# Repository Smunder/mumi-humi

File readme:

Information and project documentationa at https://smundor.de/category/mumi-humi/

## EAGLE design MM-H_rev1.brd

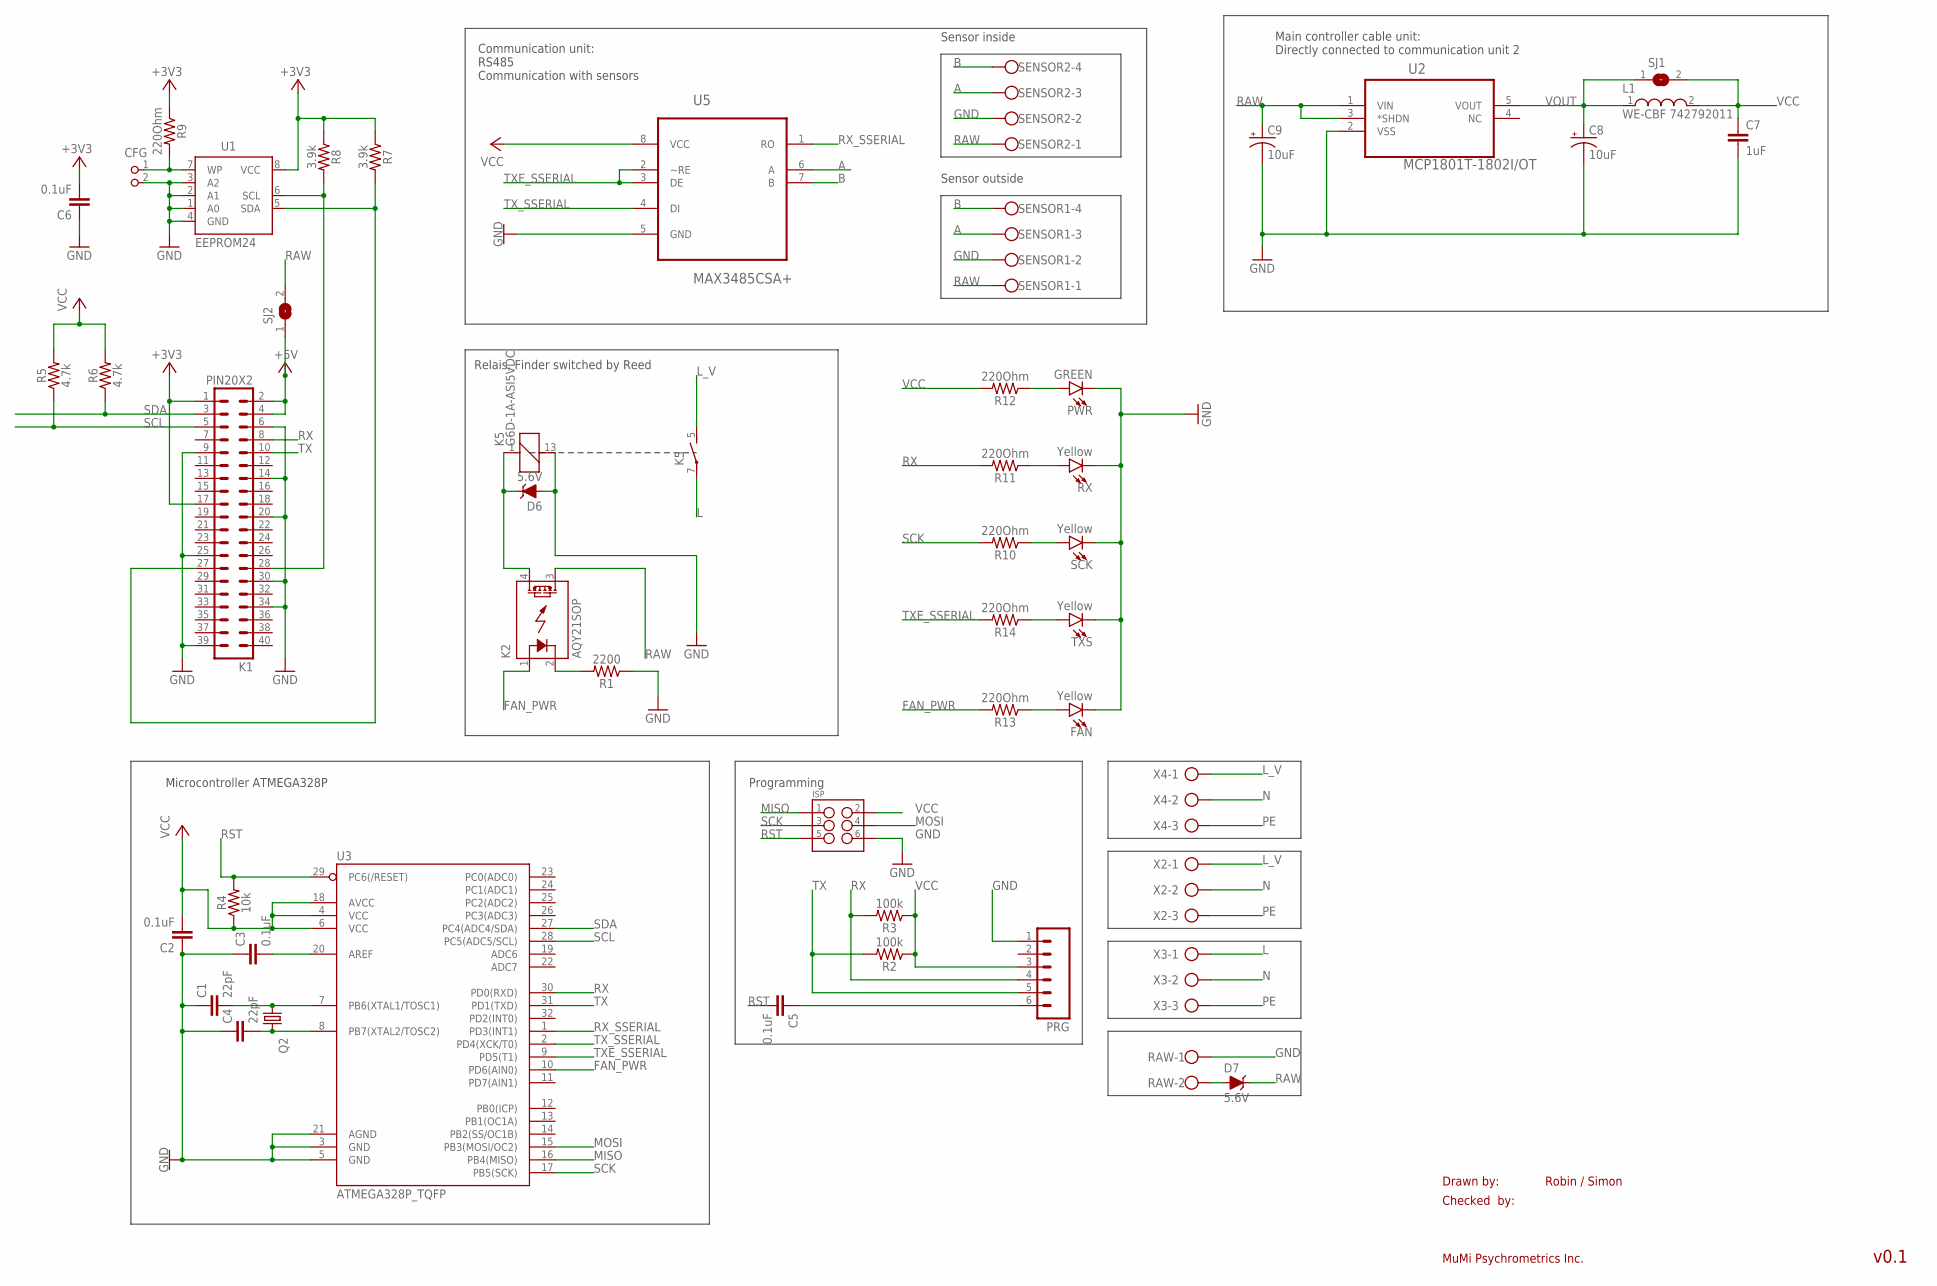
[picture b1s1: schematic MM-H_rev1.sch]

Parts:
C1, C4: 22pF; 0402
C2, C3, C5, C6: 0.1uF; 0402
C7: 1uF; 0402
C8, C9: 10uF; EIA3216
CFG: PIN2_100; PIN_W_2
D6, D7: 5.6V; SOD-323
FAN: Yellow; LED-0603
ISP: M03X2POGO_PINS; 2X3_POGO
K1: PIN20X2; PIN_20X2
K2: AQY21SOP; SOP04
K5: G6D-1A-ASI5VDC; G6D
L1: WE-CBF 742792011; WE-CBF_0805(W=3.0)
PRG: M06SILK_FEMALE_PTH; 1X06
PWR: GREEN; LED-0603
Q2: KX-K; 11.4X4.5
R1: 2200; 0402
R2, R3: 100k; 0402
R4: 10k; 0402
R5, R6: 4.7k; 0402
R7, R8: 3.9k; 0402
R9, R10, R11, R12, R13, R14: 220Ohm; 0402
RAW: W237-102
RX: Yellow; LED-0603
SCK: Yellow; LED-0603
SENSOR1, SENSOR2: W237-4
SJ1, SJ2: SJ
TXS: Yellow; LED-0603
U1: EEPROM24; SOIC8
U2: MCP1801T-1802I/OT; SOT95P270X145-5N
U3: ATMEGA328P_TQFP; TQFP32-08
U5: MAX3485CSA+; SOIC127P600X175-8N
X2, X3, X4: AK500/3

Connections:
+3V3: C6.2, K1.1, K1.17, R7.1, R8.1, R9.1, U1.8 (VCC)
+5V: K1.2, K1.4, SJ2.1
A: SENSOR1.3, SENSOR2.3, U5.6 (A)
B: SENSOR1.4, SENSOR2.4, U5.7 (B)
FAN_PWR: K2.1 (A), R13.2, U3.10 (PD6(AIN0))
GND: C1.1, C2.1, C3.1, C4.1, C6.1, C7.2, C8.C (-), C9.C (-), CFG.2, D6.A, FAN.C, ISP.P$6 (6), K1.6, K1.9, K1.14, K1.20, K1.25, K1.30, K1.34, K1.39, K5.13 (2), PRG.1, PWR.C, R1.1, RAW.1, RX.C, SCK.C, SENSOR1.2, SENSOR2.2, TXS.C, U1.1 (A0), U1.2 (A1), U1.3 (A2), U1.4 (GND), U2.2 (VSS), U3.3 (GND), U3.5 (GND), U3.21 (AGND), U5.5 (GND)
L: K5.7, X3.1
L_V: K5.5 (S), X2.1, X4.1
MISO: ISP.P$1 (1), U3.16 (PB4(MISO))
MOSI: ISP.P$4 (4), U3.15 (PB3(MOSI/OC2))
N: X2.2, X3.2, X4.2
unnamed: K1.28, R8.2, U1.6 (SCL)
unnamed: K1.27, R7.2, U1.5 (SDA)
unnamed: CFG.1, R9.2, U1.7 (WP)
unnamed: K2.2 (K), R1.2
unnamed: C5.1, PRG.6
unnamed: R11.1, RX.A
unnamed: D7.A, RAW.2
unnamed: D6.C, K2.4 (DS1), K5.1
unnamed: C3.2, U3.20 (AREF)
unnamed: PWR.A, R12.1
unnamed: R10.1, SCK.A
unnamed: R14.1, TXS.A
unnamed: FAN.A, R13.1
unnamed: C1.2, Q2.1, U3.7 (PB6(XTAL1/TOSC1))
unnamed: C4.2, Q2.2, U3.8 (PB7(XTAL2/TOSC2))
PE: X2.3, X3.3, X4.3
RAW: C9.A (+), D7.C, K2.3 (DS2), SENSOR1.1, SENSOR2.1, SJ2.2, U2.1 (VIN), U2.3 (*SHDN)
RST: C5.2, ISP.P$5 (5), R4.2, U3.29 (PC6(/RESET))
RX: K1.8, PRG.4, R3.2, R11.2, U3.30 (PD0(RXD))
RX_SSERIAL: U3.1 (PD3(INT1)), U5.1 (RO)
SCK: ISP.P$3 (3), R10.2, U3.17 (PB5(SCK))
SCL: K1.5, R5.1, U3.28 (PC5(ADC5/SCL))
SDA: K1.3, R6.1, U3.27 (PC4(ADC4/SDA))
TX: K1.10, PRG.5, R2.2, U3.31 (PD1(TXD))
TXE_SSERIAL: R14.2, U3.9 (PD5(T1)), U5.2 (~RE), U5.3 (DE)
TX_SSERIAL: U3.2 (PD4(XCK/T0)), U5.4 (DI)
VCC: C2.2, C7.1, ISP.P$2 (2), L1.2, PRG.3, R2.1, R3.1, R4.1, R5.2, R6.2, R12.2, SJ1.2, U3.4 (VCC), U3.6 (VCC), U3.18 (AVCC), U5.8 (VCC)
VOUT: C8.A (+), L1.1, SJ1.1, U2.5 (VOUT)

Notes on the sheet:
Drawn by:
Checked by:
MuMi Psychrometrics Inc.
Robin / Simon
v0.1
Communication unit: RS485 Communication with sensors
Main controller cable unit: Directly connected to communication unit 2
Programming
Microcontroller ATMEGA328P
Relais, Finder switched by Reed
Sensor inside
Sensor outside

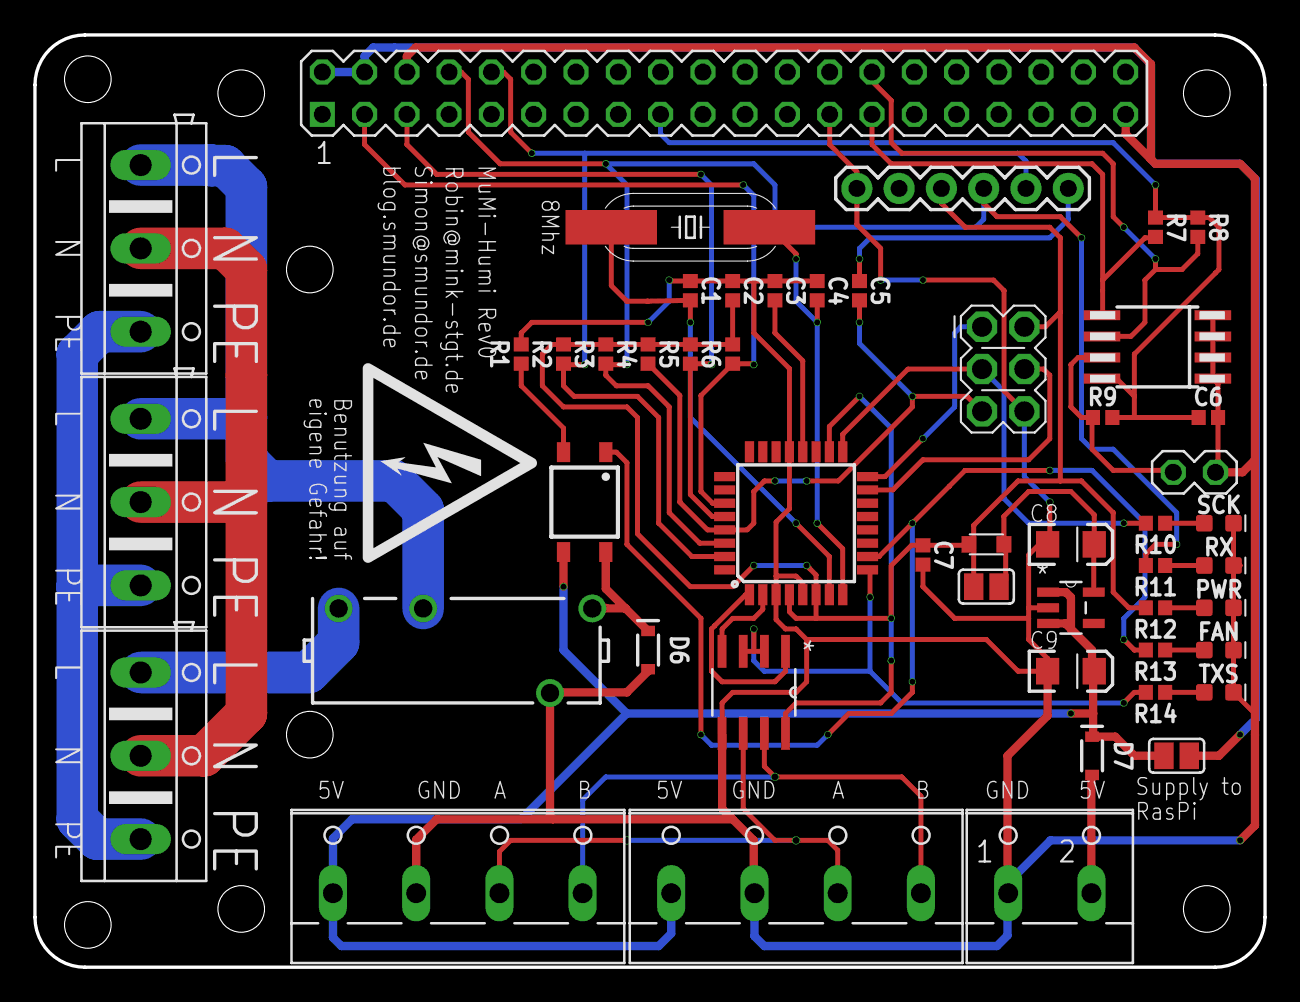
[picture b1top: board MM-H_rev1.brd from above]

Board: 2 copper layers, 73.9 x 56.0 mm, 50 parts (0 on the bottom side), 39 nets.

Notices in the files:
parts and their libraries:
SparkFun-Connectors: Licensing: Creative Commons ShareAlike 4.0 International - https://creativecommons.org/licenses/by-sa/4.0
crystal-geyer_V1_0: Copyright: Geyer-Electronic
Wurth_Elektronik_Passive_rev15f: Copyright: Würth Elektronik
